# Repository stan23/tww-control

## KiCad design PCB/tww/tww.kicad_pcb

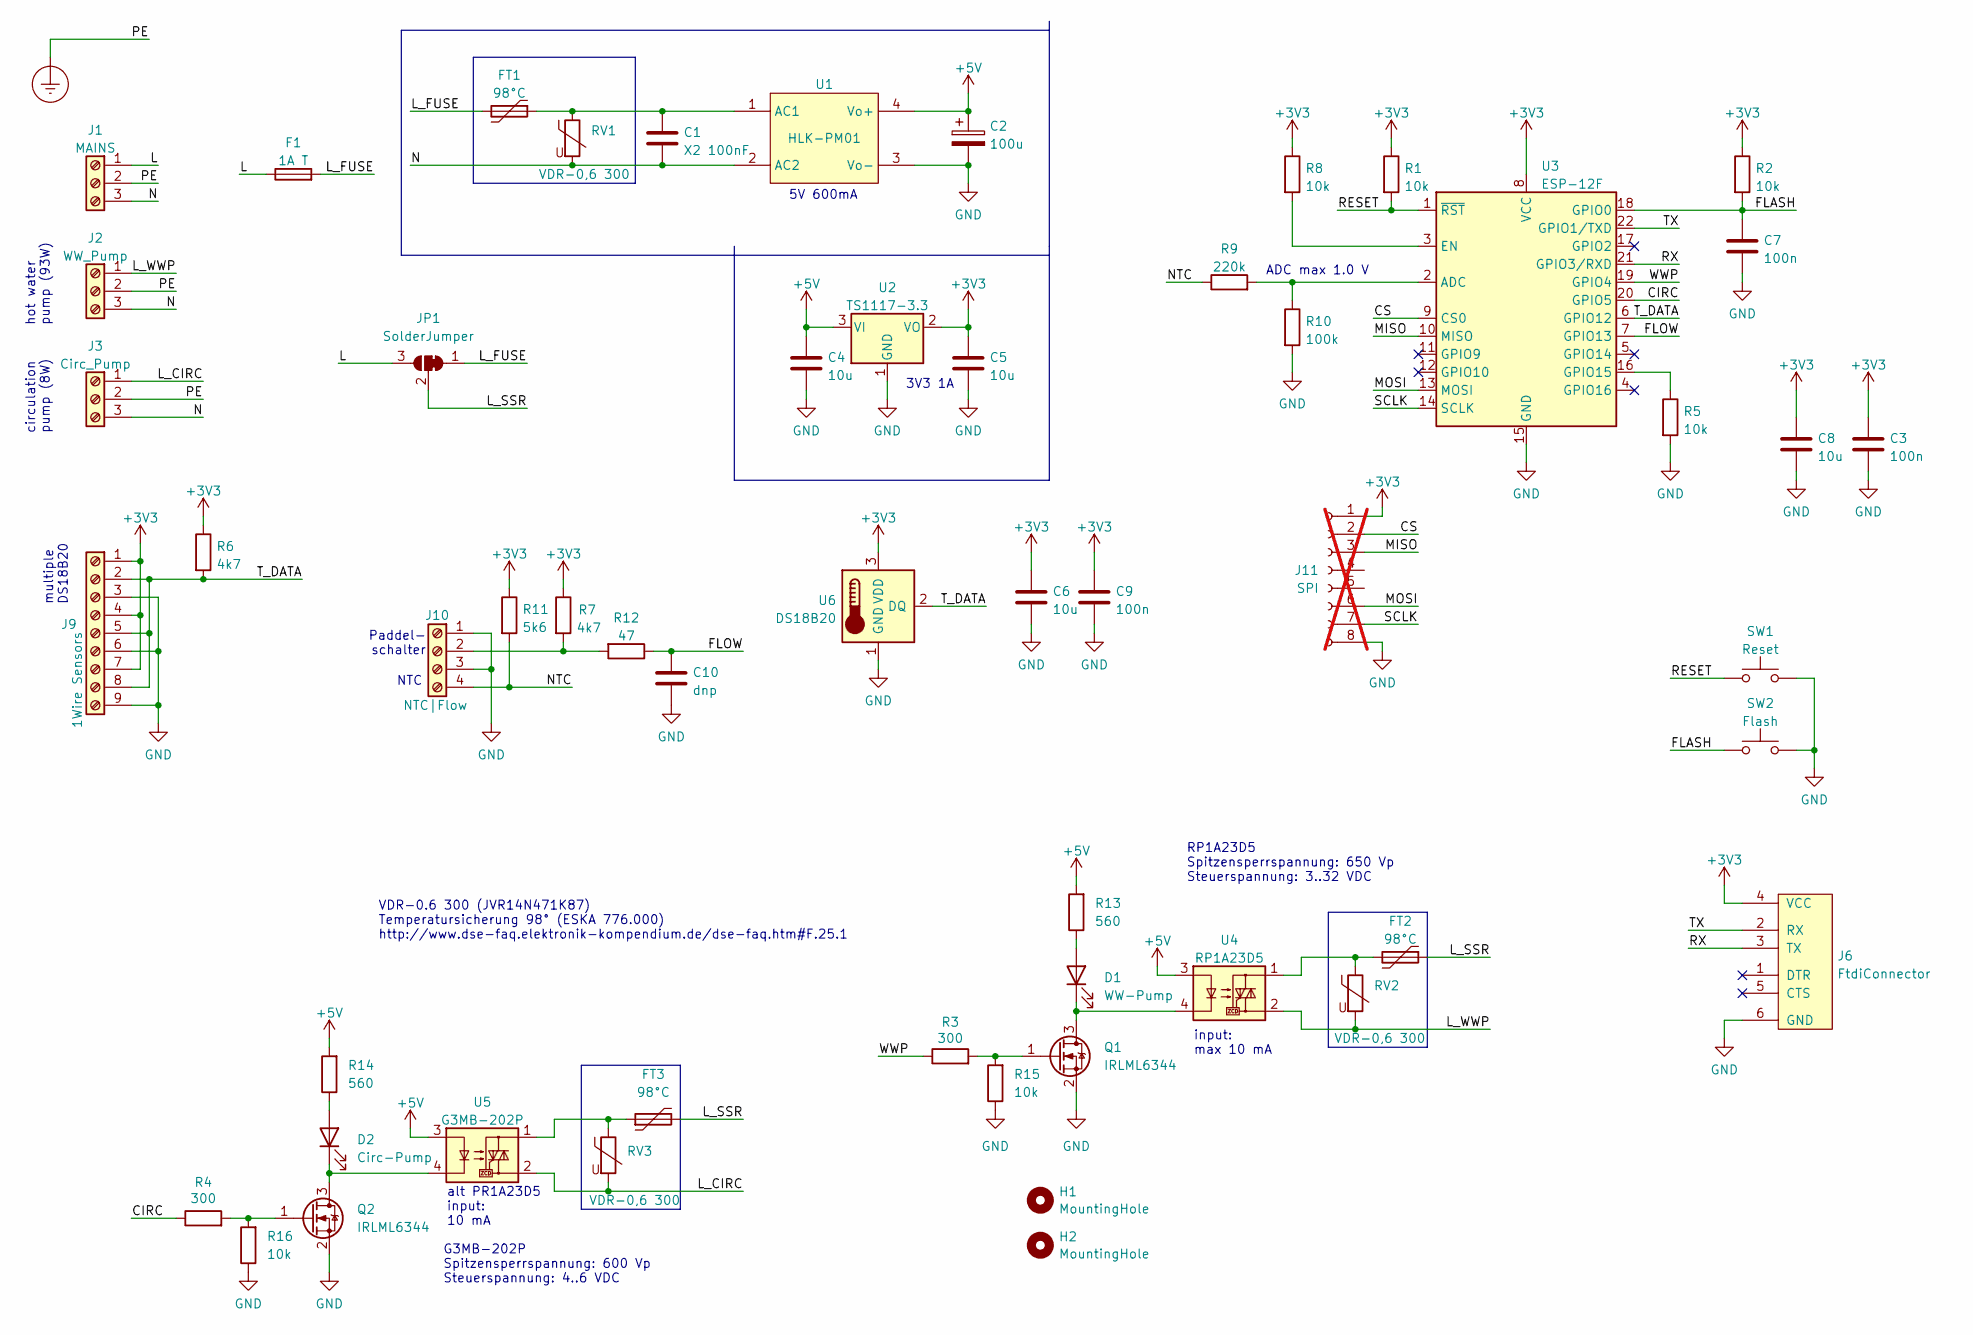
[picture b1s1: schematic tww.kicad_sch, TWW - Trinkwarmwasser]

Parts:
C1: X2 100nF; C_Rect_L13.0mm_W8.0mm_P10.00mm_FKS3_FKP3_MKS4
C2: 100u; CP_EIA-3528-12_Kemet-T_Pad1.50x2.35mm_HandSolder
C3, C7, C9: 100n; C_0805_2012Metric_Pad1.18x1.45mm_HandSolder
C4, C5, C6, C8: 10u; C_0805_2012Metric_Pad1.18x1.45mm_HandSolder
C10: dnp; C_0805_2012Metric_Pad1.18x1.45mm_HandSolder
D1: WW-Pump; LED_0805_2012Metric_Pad1.15x1.40mm_HandSolder
D2: Circ-Pump; LED_0805_2012Metric_Pad1.15x1.40mm_HandSolder
F1: 1A T; Fuseholder_TR5_Littelfuse_No560_No460
FT1, FT2, FT3: 98°C; R_Axial_DIN0411_L9.9mm_D3.6mm_P5.08mm_Vertical
H1, H2: MountingHole; MountingHole_3.2mm_M3
J1: MAINS; P-250-203
J2: WW_Pump; P-250-203
J3: Circ_Pump; P-250-203
J6: FtdiConnector; Pin_Header_Straight_1x06_Pitch2.54mm_Tight_Fit
J9: 1Wire Sensors; P-250-409
J10: NTC|Flow; P-250-404
J11: SPI; PinHeader_1x08_P2.00mm_Vertical; not fitted
JP1: SolderJumper; SolderJumper-3_P1.3mm_Bridged12_Pad1.0x1.5mm
Q1, Q2: IRLML6344; SOT-23_Handsoldering
R1, R2, R5, R8, R15, R16: 10k; R_0805_2012Metric_Pad1.20x1.40mm_HandSolder
R3, R4: 300; R_0805_2012Metric_Pad1.20x1.40mm_HandSolder
R6, R7: 4k7; R_0805_2012Metric_Pad1.20x1.40mm_HandSolder
R9: 220k; R_0805_2012Metric_Pad1.20x1.40mm_HandSolder
R10: 100k; R_0805_2012Metric_Pad1.20x1.40mm_HandSolder
R11: 5k6; R_0805_2012Metric_Pad1.20x1.40mm_HandSolder
R12: 47; R_0805_2012Metric_Pad1.20x1.40mm_HandSolder
R13, R14: 560; R_0805_2012Metric_Pad1.20x1.40mm_HandSolder
RV1, RV2, RV3: VDR-0,6 300; RV_Disc_D12mm_W3.9mm_P7.5mm
SW1: Reset; SW_SPST_CK_RS282G05A3
SW2: Flash; SW_SPST_CK_RS282G05A3
U1: HLK-PM01; Hi-Link_HLK-PMxx
U2: TS1117-3.3; SOT-223-3_TabPin2
U3: ESP-12F; ESP-12E
U4: RP1A23D5; Carlo_Gavazzi_RP1A
U5: G3MB-202P; Omron_G3MB
U6: DS18B20; TO-92_Inline

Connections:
+3V3: C3.1, C5.1, C6.1, C8.1, C9.1, J6.4 (VCC), J9.1, J9.4, J9.7, J11.1, R1.1, R2.1, R6.1, R7.1, R8.1, R11.1, U2.2 (VO), U3.8 (VCC), U6.3 (VDD)
+5V: C2.1, C4.1, R13.2, R14.2, U1.4 (Vo+), U2.3 (VI), U4.3, U5.3
/CIRC: R4.1, U3.20 (GPIO5)
/CS: J11.2, U3.9 (CS0)
/FLASH: C7.1, R2.2, SW2.1, U3.18 (GPIO0)
/FLOW: C10.1, R12.1, U3.7 (GPIO13)
/L: F1.1, J1.1, JP1.3 (B)
/L_CIRC: J3.1, RV3.2, U5.2
/L_FUSE: F1.2, FT1.2, JP1.1 (A)
/L_SSR: FT2.1, FT3.2, JP1.2 (C)
/L_WWP: J2.1, RV2.2, U4.2
/MISO: J11.3, U3.10 (MISO)
/MOSI: J11.6, U3.13 (MOSI)
/N: C1.2, J1.3, J2.3, J3.3, RV1.2, U1.2 (AC2)
/NTC: J10.4, R9.1, R11.2
/RESET: R1.2, SW1.1, U3.1 (~RST)
/RX: J6.3 (TX), U3.21 (GPIO3/RXD)
/SCLK: J11.7, U3.14 (SCLK)
/TX: J6.2 (RX), U3.22 (GPIO1/TXD)
/T_DATA: J9.2, J9.5, J9.8, R6.2, U3.6 (GPIO12), U6.2 (DQ)
/WWP: R3.1, U3.19 (GPIO4)
Earth_Protective: J1.2, J2.2, J3.2
GND: C2.2, C3.2, C4.2, C5.2, C6.2, C7.2, C8.2, C9.2, C10.2, J6.6 (GND), J9.3, J9.6, J9.9, J10.1, J10.3, J11.8, Q1.2 (S), Q2.2 (S), R5.2, R10.2, R15.1, R16.1, SW1.2, SW2.2, U1.3 (Vo-), U2.1 (GND), U3.15 (GND), U6.1 (GND)
unnamed: D1.2 (A), R13.1
unnamed: D1.1 (K), Q1.3 (D), U4.4
unnamed: D2.2 (A), R14.1
unnamed: D2.1 (K), Q2.3 (D), U5.4
unnamed: FT2.2, RV2.1, U4.1
unnamed: FT3.1, RV3.1, U5.1
unnamed: J10.2, R7.2, R12.2
unnamed: Q1.1 (G), R3.2, R15.2
unnamed: Q2.1 (G), R4.2, R16.2
unnamed: C1.1, FT1.1, RV1.1, U1.1 (AC1)
unnamed: R9.2, R10.1, U3.2 (ADC)
unnamed: R8.2, U3.3 (EN)
unnamed: R5.1, U3.16 (GPIO15)

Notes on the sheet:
hot water pump (93W)
VDR-0.6 300 (JVR14N471K87) Temperatursicherung 98° (ESKA 776.000) http://www.dse-faq.elektronik-kompendium.de/dse-faq.htm#F.25.1
input: max 10 mA
ADC max 1.0 V
3V3 1A
Paddel- schalter
alt PR1A23D5 input: 10 mA
G3MB-202P Spitzensperrspannung: 600 Vp Steuerspannung: 4..6 VDC
5V 600mA
NTC
RP1A23D5 Spitzensperrspannung: 650 Vp Steuerspannung: 3..32 VDC
circulation pump (8W)
multiple DS18B20

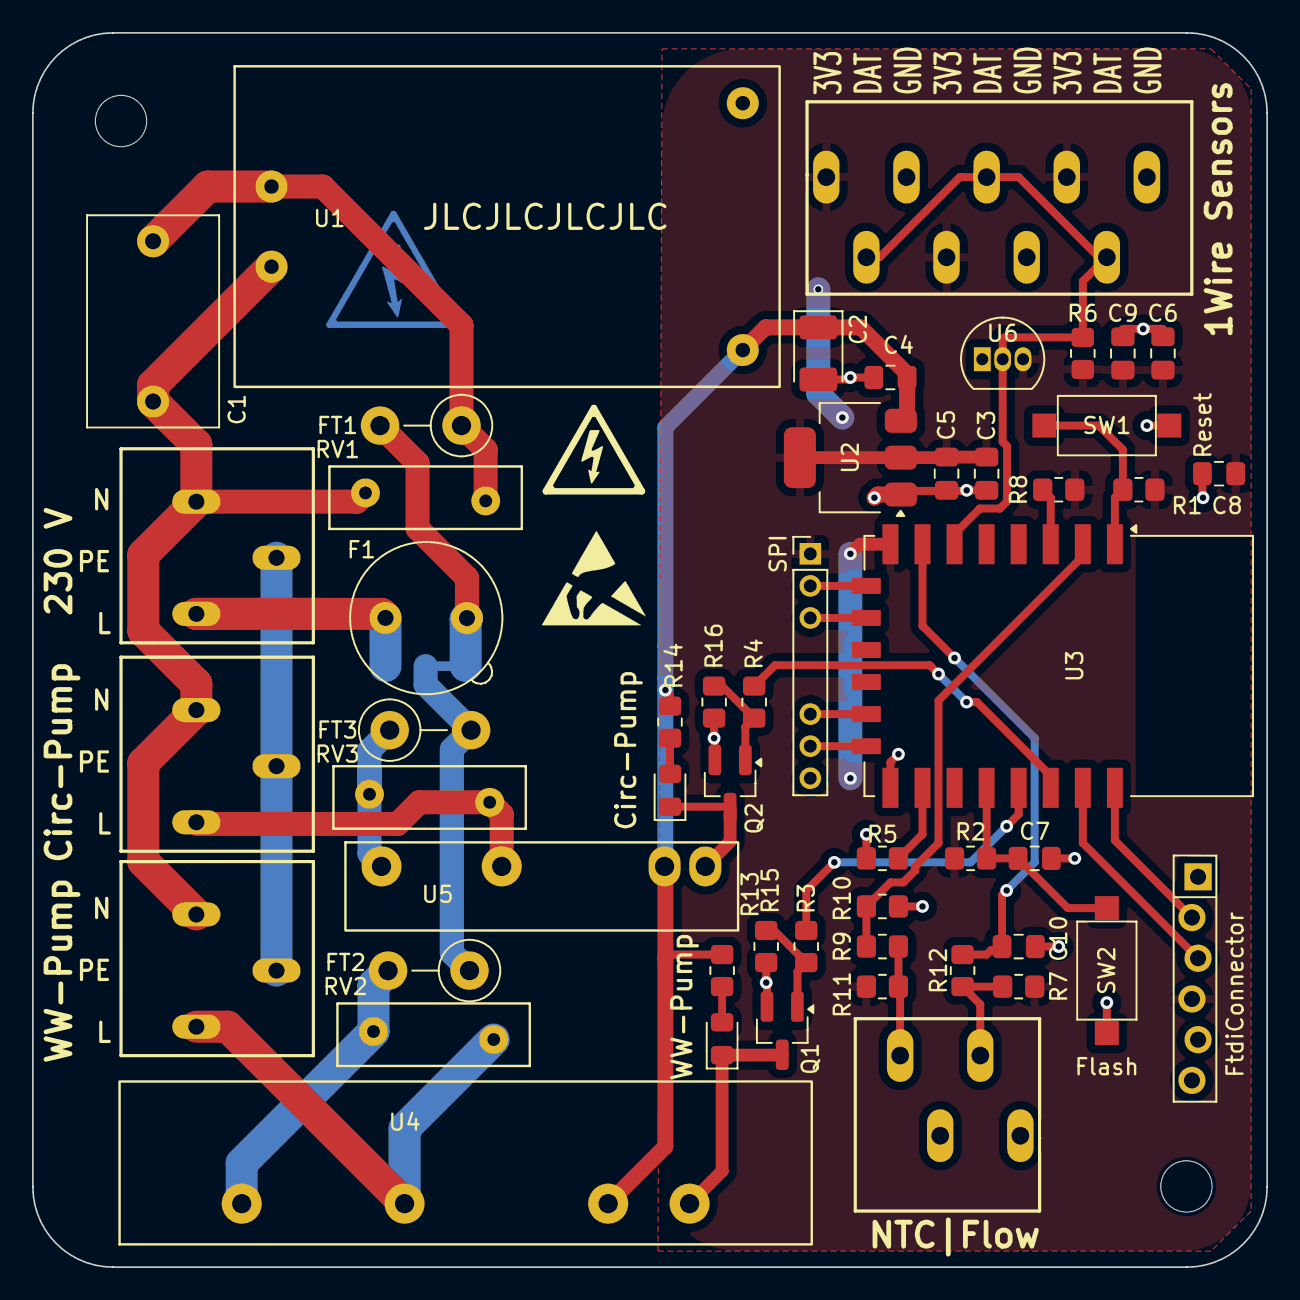
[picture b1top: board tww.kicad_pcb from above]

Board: 2 copper layers, 77.0 x 77.0 mm, 55 parts (1 on the bottom side), 36 nets.

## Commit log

2024-10-19 PCB version 1.0
2024-10-22 update to PCB v1.1
    addresses #1
    - U1 (HLK-PM01) output polarity swapped
    - J6 (FtdiConnector): RX and TX swapped
    - J10 label fixed
    - VDR-0.6 footprint changed
    - replaced BC547 by FET IRLML6344
2024-11-15 updates for PCB version 1.1
    - reconnect WWP and CIRC outputs

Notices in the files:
PCB/tww/tww.kicad_pcb:
CC BY-NC-SA
PCB/tww/tww.kicad_sch:
CC BY-NC-SA 4.0
